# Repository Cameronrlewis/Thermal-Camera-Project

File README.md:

# Thermal-Camera-Project
Repository for a new PCB Project

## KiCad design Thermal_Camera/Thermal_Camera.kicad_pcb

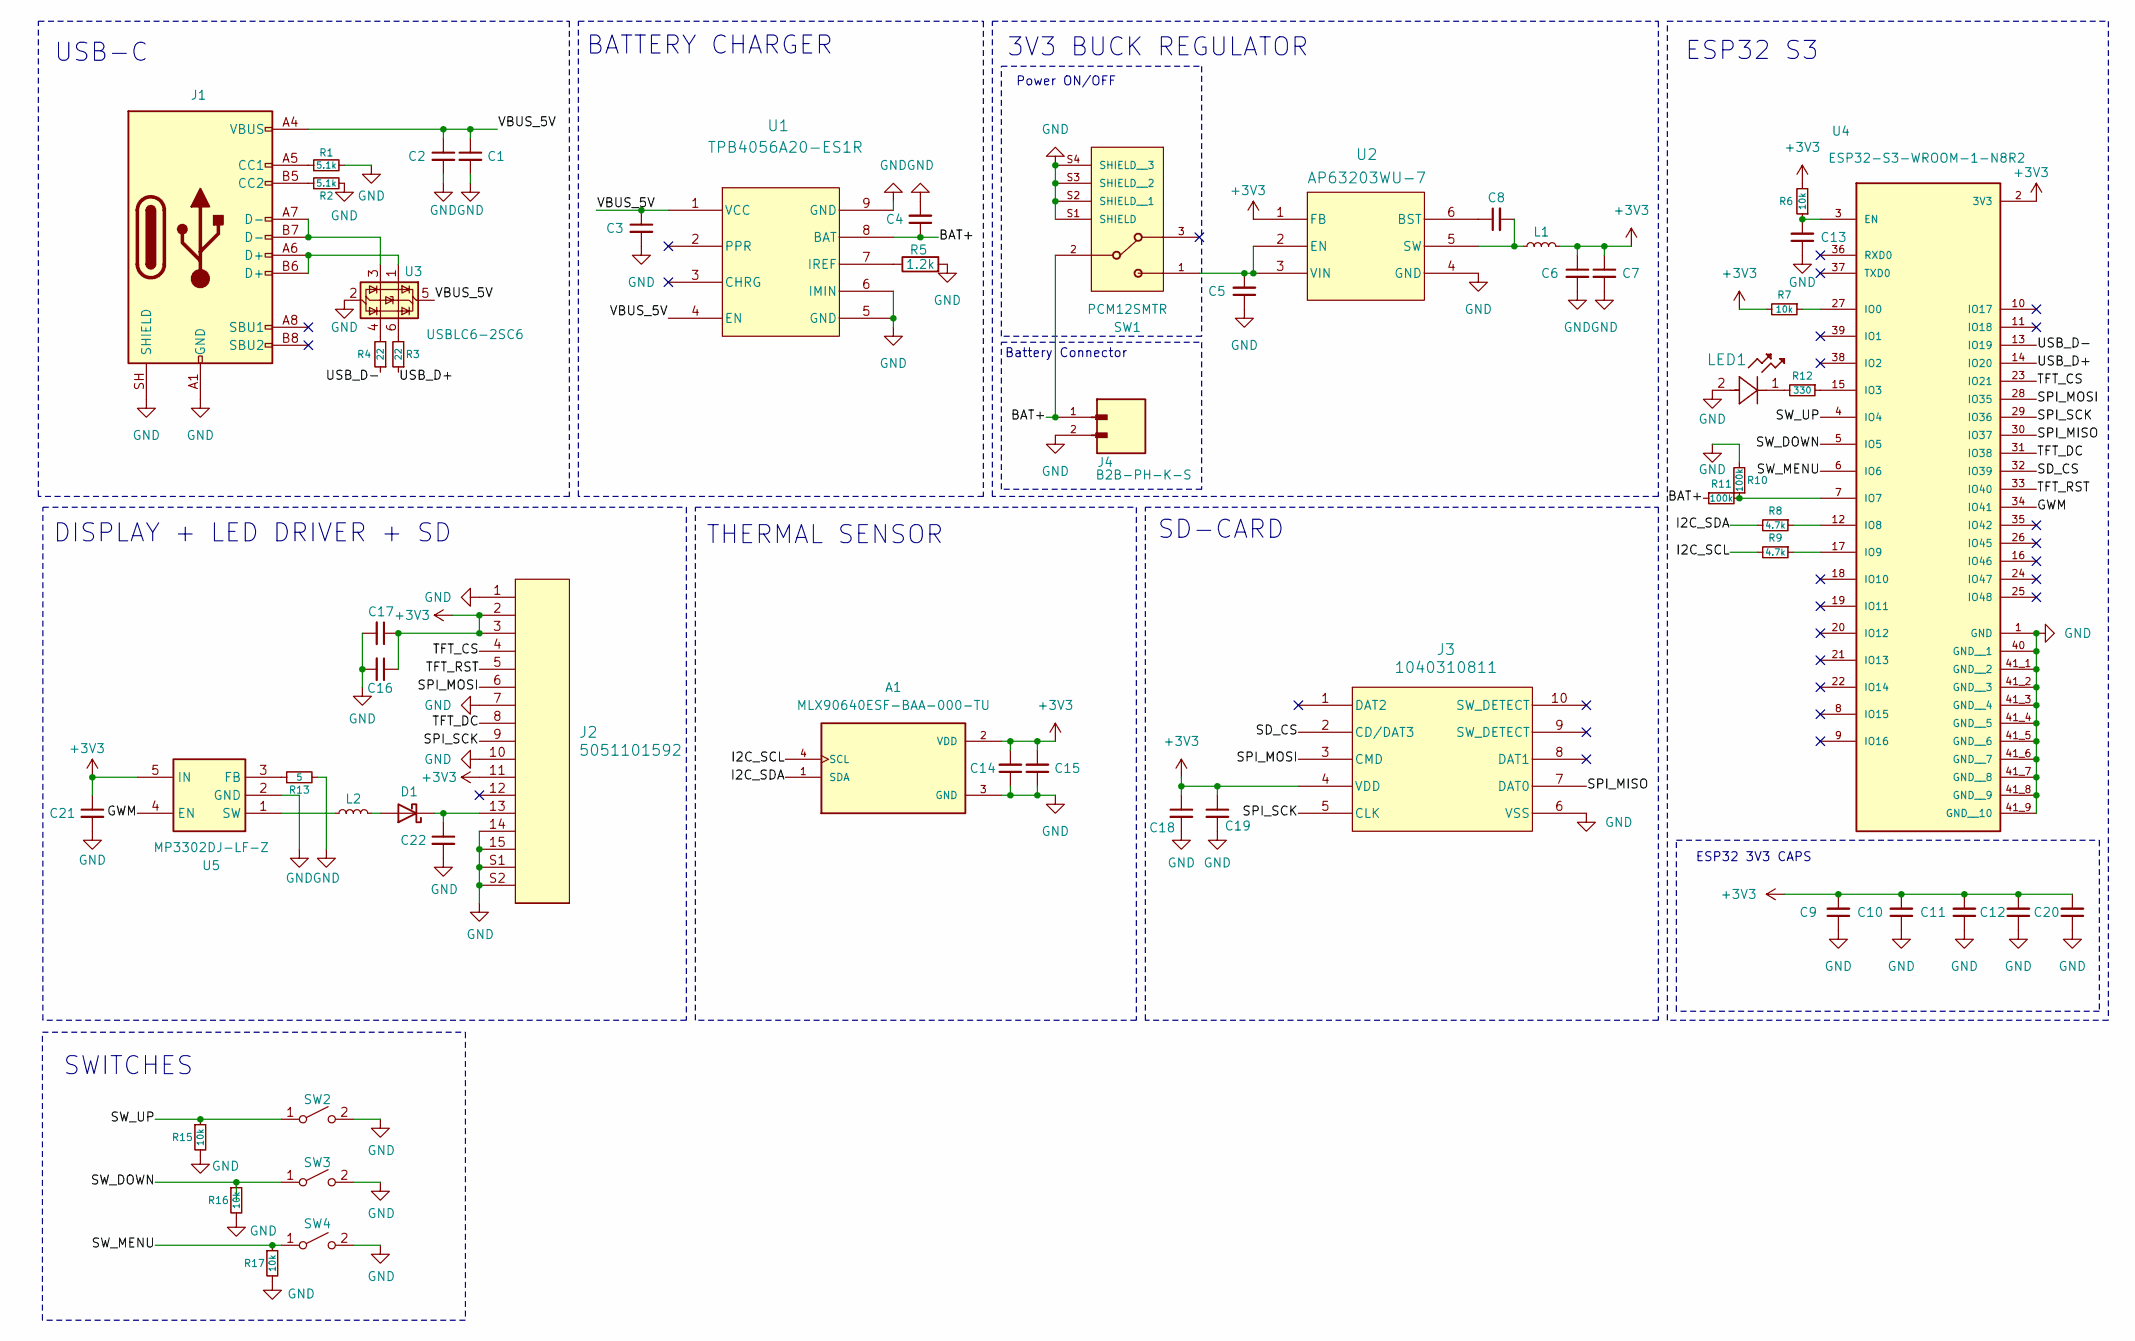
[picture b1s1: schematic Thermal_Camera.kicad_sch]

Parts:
A1: MLX90640ESF-BAA-000-TU; TO-39_4P-BD9.3_MLX90640ESF-BAA-000-TU_H5.7; PARTREV 11
C1, C3, C4, C5, C20: 10uF; C_0805_2012Metric_Pad1.18x1.45mm_HandSolder
C2, C8, C9, C10, C11, C14, C16, C19: 0.1uF; C_0805_2012Metric_Pad1.18x1.45mm_HandSolder
C6, C7: 22uF; C_0805_2012Metric_Pad1.18x1.45mm_HandSolder
C12, C13, C21, C22: 1uF; C_0805_2012Metric_Pad1.18x1.45mm_HandSolder
C15, C17, C18: 4.7uF; C_0805_2012Metric_Pad1.18x1.45mm_HandSolder
D1: D_Schottky; SOD2512X115N
J1: USB_C_Receptacle_USB2.0; USB_C_Receptacle_HRO_TYPE-C-31-M-12
J2: 5051101592; CON_5051101592_MOL
J3: 1040310811; 104031-0811_MOL
J4: B2B-PH-K-S; CONN-TH_B2B-PH-K-S
L1: 3.9uH; IND_4030
L2: 3.9uH; IND_LQH2MCN4R7M02L
LED1: LTST-C170KGKT; LED0603-RD
R1, R2: 5.1k; R_0805_2012Metric_Pad1.20x1.40mm_HandSolder
R3, R4: 22; R_0805_2012Metric_Pad1.20x1.40mm_HandSolder
R5: 1.2k; R_0805_2012Metric_Pad1.20x1.40mm_HandSolder
R6, R7, R15, R16, R17: 10k; R_0805_2012Metric_Pad1.20x1.40mm_HandSolder
R8, R9: 4.7k; R_0805_2012Metric_Pad1.20x1.40mm_HandSolder
R10, R11: 100k; R_0805_2012Metric_Pad1.20x1.40mm_HandSolder
R12: 330; R_0805_2012Metric_Pad1.20x1.40mm_HandSolder
R13: 5; R_0805_2012Metric_Pad1.20x1.40mm_HandSolder
SW1: PCM12SMTR; SW-SMD_PCM12SMTR
SW2, SW3, SW4: TS-1088R-02526; SW-SMD_4P-L5.1-W5.1-P3.70-LS6.5-TL_H1.5
U1: TPB4056A20-ES1R; ESOP-8_L4.9-W3.9-P1.27-LS6.0-BL-EP
U2: AP63203WU-7; TSOT-26_L2.9-W1.6-P0.95-LS2.8-BL
U3: USBLC6-2SC6; SOT-23-6
U4: ESP32-S3-WROOM-1-N8R2; WIRELM-SMD_ESP32-S3-WROOM-1; PARTREV v1.0
U5: MP3302DJ-LF-Z; SOT95P280X100-5N; Manufacturer_Part_Number MP3302DJ-LF-Z; Mouser Part Number 946-MP3302DJLFZ

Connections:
+3V3: A1.2 (VDD), C6.1, C7.1, C9.2, C10.2, C11.2, C12.2, C14.2, C15.2, C16.1, C17.1, C18.1, C19.1, C20.2, C21.1, J2.2, J2.3, J2.11, J3.4 (VDD), L1.2, R6.2, R7.2, U2.1 (FB), U4.2 (3V3), U5.5 (IN)
/BAT+: C4.1, J4.1, R11.1, SW1.2, U1.8 (BAT)
/GWM: U4.34 (IO41), U5.4 (EN)
/I2C_SCL: A1.4 (SCL), R9.2
/I2C_SDA: A1.1 (SDA), R8.2
/SD_CS: J3.2 (CD/DAT3), U4.32 (IO39)
/SPI_MISO: J3.7 (DAT0), U4.30 (IO37)
/SPI_MOSI: J2.6, J3.3 (CMD), U4.28 (IO35)
/SPI_SCK: J2.9, J3.5 (CLK), U4.29 (IO36)
/SW_DOWN: R16.1, SW3.1 (A), U4.5 (IO5)
/SW_MENU: R17.1, SW4.1 (A), U4.6 (IO6)
/SW_UP: R15.1, SW2.1 (A), U4.4 (IO4)
/TFT_CS: J2.4, U4.23 (IO21)
/TFT_DC: J2.8, U4.31 (IO38)
/TFT_RST: J2.5, U4.33 (IO40)
/USB_D+: R3.1, U4.14 (IO20)
/USB_D-: R4.1, U4.13 (IO19)
/VBUS_5V: C1.1, C2.1, C3.1, J1.A4 (VBUS), J1.A9 (VBUS), J1.B4 (VBUS), J1.B9 (VBUS), U1.1 (VCC), U1.4 (EN), U3.5 (VBUS)
GND: A1.3 (GND), C1.2, C2.2, C3.2, C4.2, C5.1, C6.2, C7.2, C9.1, C10.1, C11.1, C12.1, C13.1, C14.1, C15.1, C16.2, C17.2, C18.2, C19.2, C20.1, C21.2, C22.2, J1.A1 (GND), J1.A12 (GND), J1.B1 (GND), J1.B12 (GND), J1.SH (SHIELD), J2.1, J2.7, J2.10, J2.14, J2.15, J2.S1, J2.S2, J3.6 (VSS), J4.2, LED1.2, R1.2, R2.2, R5.2, R10.2, R13.2, R15.2, R16.2, R17.2, SW1.S1 (SHIELD), SW1.S2 (SHIELD__1), SW1.S3 (SHIELD__2), SW1.S4 (SHIELD__3), SW2.2 (B), SW3.2 (B), SW4.2 (B), U1.5 (GND), U1.6 (IMIN), U1.9 (GND), U2.4 (GND), U3.2 (GND), U4.1 (GND), U4.40 (GND__1), U4.41_1 (GND__2), U4.41_2 (GND__3), U4.41_3 (GND__4), U4.41_4 (GND__5), U4.41_5 (GND__6), U4.41_6 (GND__7), U4.41_7 (GND__8), U4.41_8 (GND__9), U4.41_9 (GND__10), U5.2 (GND)
unnamed: C22.1, D1.C (K), J2.13
unnamed: D1.A, L2.2
unnamed: J1.A5 (CC1), R1.1
unnamed: J1.B5 (CC2), R2.1
unnamed: J1.A6 (D+), J1.B6 (D+), U3.1 (I/O1)
unnamed: J1.A7 (D-), J1.B7 (D-), U3.3 (I/O2)
unnamed: LED1.1, R12.2
unnamed: R3.2, U3.6 (I/O1)
unnamed: R4.2, U3.4 (I/O2)
unnamed: R5.1, U1.7 (IREF)
unnamed: C8.1, U2.6 (BST)
unnamed: C5.2, SW1.1, U2.2 (EN), U2.3 (VIN)
unnamed: C8.2, L1.1, U2.5 (SW)
unnamed: C13.2, R6.1, U4.3 (EN)
unnamed: R7.1, U4.27 (IO0)
unnamed: R12.1, U4.15 (IO3)
unnamed: R10.1, R11.2, U4.7 (IO7)
unnamed: R8.1, U4.12 (IO8)
unnamed: R9.1, U4.17 (IO9)
unnamed: R13.1, U5.3 (FB)
unnamed: L2.1, U5.1 (SW)

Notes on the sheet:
DISPLAY + LED DRIVER + SD
SWITCHES
SD-CARD
Power ON/OFF
ESP32 3V3 CAPS
BATTERY CHARGER
3V3 BUCK REGULATOR
ESP32 S3
USB-C
Battery Connector
THERMAL SENSOR

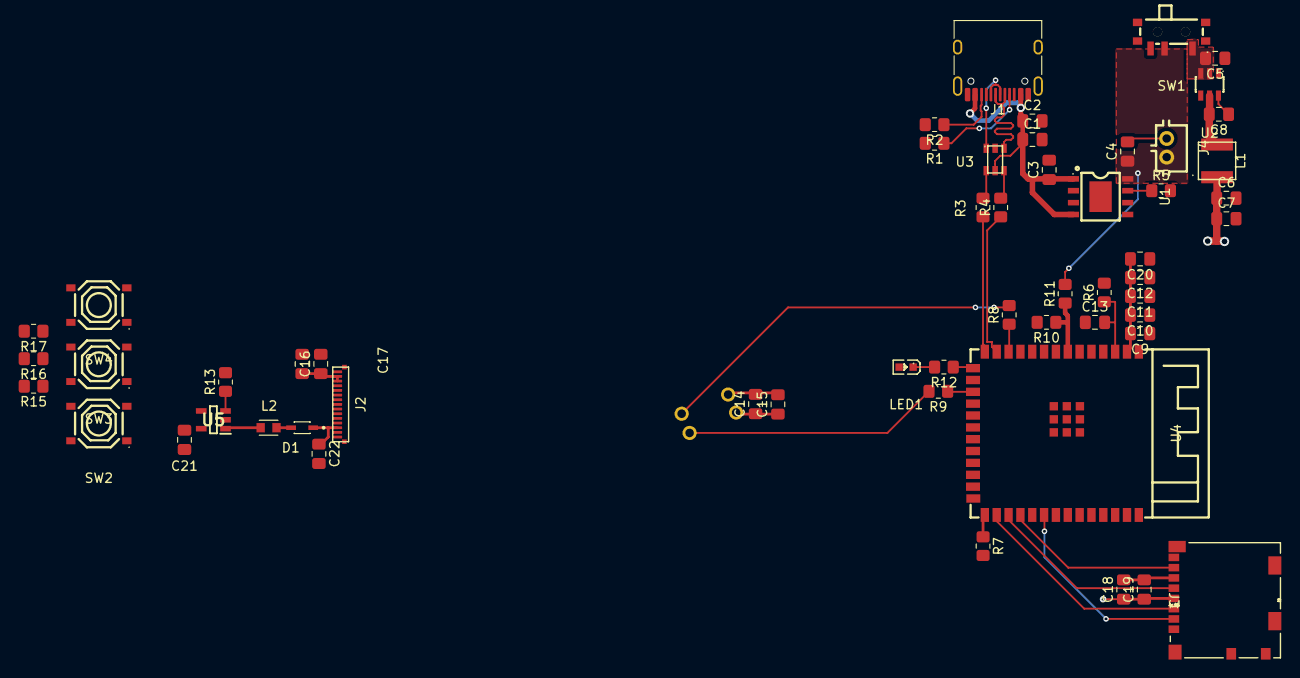
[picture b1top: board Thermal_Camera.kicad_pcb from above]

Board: 2 copper layers, 56 parts (1 on the bottom side), 40 nets.

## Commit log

2026-03-19 Project Creation
    Project and Library files
2026-03-19 Imported Component Libraries
    Symbols, 3D STL's, and Footprints
2026-03-19 Schematic
    Drew up Schematic
2026-03-24 New Libraries
    Modified component choice, added new capacitor, and created new libraries
2026-04-06 Component addition, Schematic revision, and Layout
    Added LED booster driver IC for LCD screen, updated libraries, and got the general layout finished, I need to calculate screen and battery dimensions for the final revisions.
